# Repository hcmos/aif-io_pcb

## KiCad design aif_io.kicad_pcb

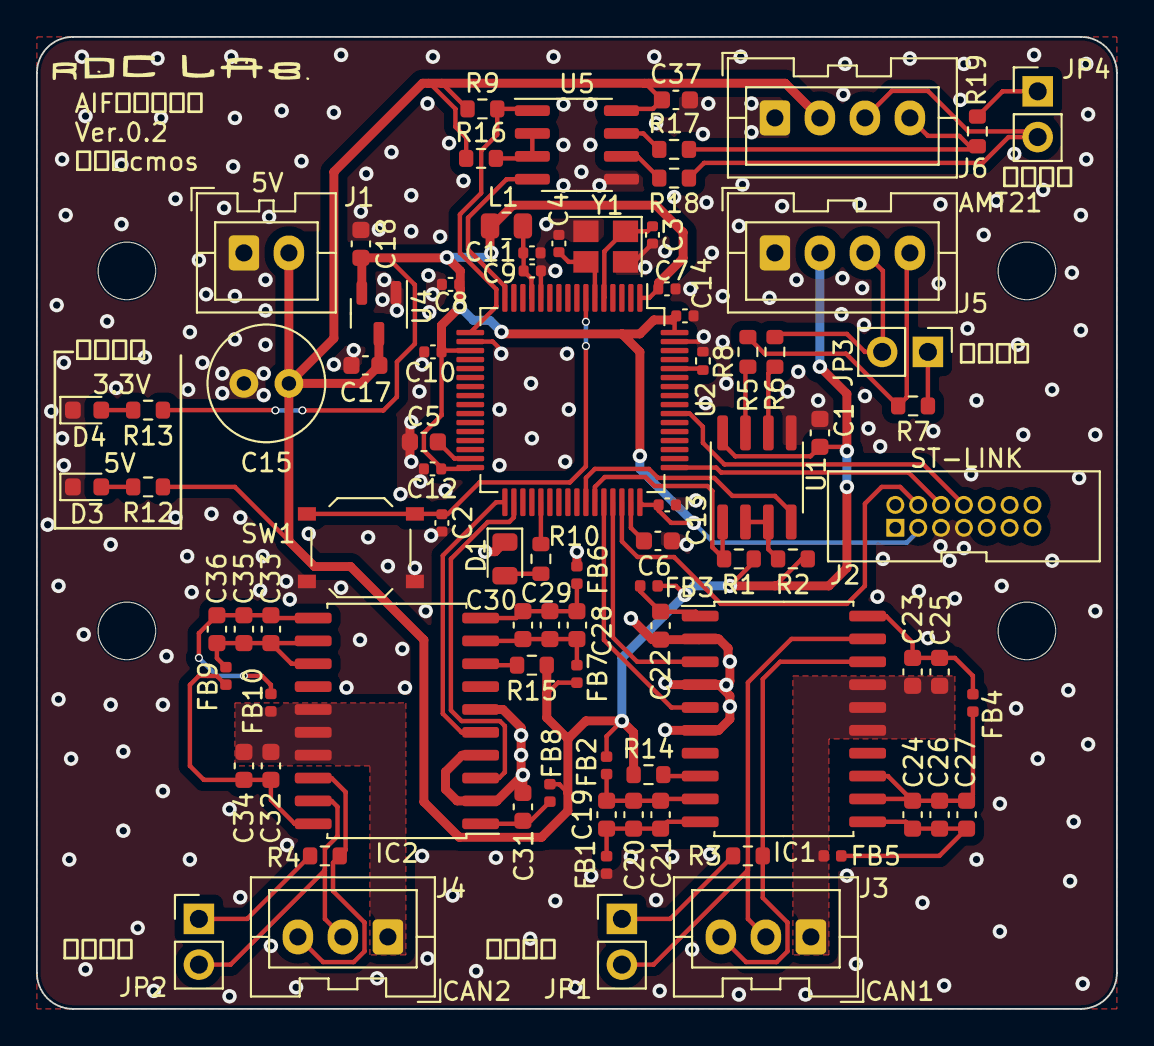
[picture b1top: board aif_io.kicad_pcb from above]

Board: 2 copper layers, 60.0 x 54.0 mm, 90 parts (0 on the bottom side), 59 nets.

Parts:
C1, C22, C23, C31, C32, C37: 0.1u; C_0603_1608Metric
C2, C7, C10, C11, C12, C13, C14: 0.1u; C_0402_1005Metric
C3, C4: 18p; C_0402_1005Metric
C5, C6: 2.2u; C_0603_1608Metric
C8: 4.7u; C_0402_1005Metric
C9: 1u; C_0402_1005Metric
C15: 100u; C_Radial_D6.3mm_H11.0mm_P2.50mm
C17, C18, C20, C26, C29, C35: 1u; C_0603_1608Metric
C19, C25, C27, C28, C34, C36: 10u; C_0603_1608Metric
C21, C24, C30, C33: 10n; C_0603_1608Metric
D1: LED; LED_0805_2012Metric
D3, D4: LED; LED_0603_1608Metric
FB1, FB2, FB3, FB4, FB5, FB6, FB7, FB8, FB9, FB10: FerriteBead; L_0402_1005Metric
H1, H2, H3, H4: MountingHole; MountingHole_3.2mm_M3
IC1, IC2: ISOW1044BDFMR; SOIC-20W_7.5x12.8mm_P1.27mm
J1: PWR; JST_XA_B02B-XASK-1_1x02_P2.50mm_Vertical
J2: ST-LINK; JTAG_BOX_CONN
J3, J4: CAN; JST_XA_B03B-XASK-1_1x03_P2.50mm_Vertical
J5, J6: AMT21; JST_XA_B04B-XASK-1_1x04_P2.50mm_Vertical
JP1, JP2, JP3, JP4: Jumper_2_Open; PinHeader_1x02_P2.54mm_Vertical
L1: 600@100MHz; R_0805_2012Metric
R1, R2, R9, R16: 10k; R_0603_1608Metric
R3, R4, R7, R19: 120; R_0603_1608Metric
R5, R6, R17, R18: 10; R_0603_1608Metric
R8: 10k; R_0402_1005Metric
R10, R13: 1.2k; R_0603_1608Metric
R12: 3.3k; R_0603_1608Metric
R14, R15: 4.7k; R_0603_1608Metric
SW1: SW_Push; SW_Push_1P1T_XKB_TS-1187A
U1, U5: THVD1420D; SOIC-8_3.9x4.9mm_P1.27mm
U2: STM32F405RGTx; LQFP-64_10x10mm_P0.5mm
U4: XC6206P332MR; SOT-23-3
Y1: 25MHz; Crystal_SMD_3225-4Pin_3.2x2.5mm

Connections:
+3.3V: C7.1, C8.1, C10.1, C12.1, C13.1, C14.1, C18.1, J2.3, L1.1, R13.1, U2.1 (VBAT), U2.19 (VDD), U2.32 (VDD), U2.48 (VDD), U2.64 (VDD), U4.2 (VO)
+5V: C1.1, C15.1, C17.1, C37.1, FB2.1, FB3.1, FB7.1, FB8.1, J1.2, J5.2, J6.2, R1.1, R2.1, R9.1, R12.1, R14.1, R15.1, R16.1, U1.8 (VCC), U4.3 (VI), U5.8 (VCC)
/CAN_Transceiver1/CAN_H: IC1.19 (CANH), J3.2, JP1.2 (B)
/CAN_Transceiver1/CAN_L: IC1.18 (CANL), J3.3, R3.2
/CAN_Transceiver1/CAN_RX: IC1.5 (RXD), U2.44 (PA11)
/CAN_Transceiver1/CAN_TX: IC1.3 (TXD), U2.45 (PA12)
/CAN_Transceiver1/GND_CAN: C23.2, C25.2, FB5.2, IC1.15 (GISOIN_1), IC1.16 (GISOIN_2), IC1.17 (GISOIN_3), J3.1
/CAN_Transceiver2/CAN_H: IC2.19 (CANH), J4.2, JP2.2 (B)
/CAN_Transceiver2/CAN_L: IC2.18 (CANL), J4.3, R4.2
/CAN_Transceiver2/CAN_RX: IC2.5 (RXD), U2.33 (PB12)
/CAN_Transceiver2/CAN_TX: IC2.3 (TXD), U2.34 (PB13)
/CAN_Transceiver2/GND_CAN: C32.2, C34.2, FB10.2, IC2.15 (GISOIN_1), IC2.16 (GISOIN_2), IC2.17 (GISOIN_3), J4.1
/CYCLE_LED: R10.1, U2.37 (PC6)
/STM32F405/SWCLK: J2.6, U2.49 (PA14)
/STM32F405/SWDIO: J2.4, U2.46 (PA13)
/STM32F405/SWO: J2.8, U2.55 (PB3)
/USART1_RX: R1.2, U1.1 (RO), U2.43 (PA10)
/USART1_TX: U1.4 (DI), U2.42 (PA9)
/USART2_RX: R9.2, U2.17 (PA3), U5.1 (RO)
/USART2_TX: U2.16 (PA2), U5.4 (DI)
GND: C1.2, C2.2, C3.2, C4.2, C5.2, C6.2, C7.2, C8.2, C9.2, C10.2, C11.2, C12.2, C13.2, C14.2, C15.2, C17.2, C18.2, C22.2, C31.2, C37.2, D1.1 (K), D3.1 (K), D4.1 (K), FB1.1, FB6.1, IC1.2 (IN), IC1.4 (STB), IC1.6 (GNDIO), IC2.2 (IN), IC2.4 (STB), IC2.6 (GNDIO), J1.1, J2.5, J2.7, J5.1, J6.1, R8.2, SW1.1, U1.5 (GND), U2.12 (VSSA), U2.18 (VSS), U2.63 (VSS), U4.1 (GND), U5.5 (GND), Y1.2, Y1.4
unnamed: D1.2 (A), R10.2
unnamed: D3.2 (A), R12.2
unnamed: D4.2 (A), R13.2
unnamed: IC1.8 (EN/FLT), R14.2
unnamed: C19.2, C20.2, C21.2, FB1.2, IC1.10 (GND1)
unnamed: C24.2, C26.2, C27.2, FB5.1, IC1.11 (GND2)
unnamed: C19.1, C20.1, C21.1, FB2.2, IC1.9 (VDD)
unnamed: C22.1, FB3.2, IC1.1 (VIO)
unnamed: C23.1, C25.1, FB4.2, IC1.20 (VISOIN)
unnamed: C24.1, C26.1, C27.1, FB4.1, IC1.12 (VISOOUT), IC1.13 (VSIN)
unnamed: IC2.8 (EN/FLT), R15.2
unnamed: C28.2, C29.2, C30.2, FB6.2, IC2.10 (GND1)
unnamed: C33.2, C35.2, C36.2, FB10.1, IC2.11 (GND2)
unnamed: C28.1, C29.1, C30.1, FB7.2, IC2.9 (VDD)
unnamed: C31.1, FB8.2, IC2.1 (VIO)
unnamed: C32.1, C34.1, FB9.2, IC2.20 (VISOIN)
unnamed: C33.1, C35.1, C36.1, FB9.1, IC2.12 (VISOOUT), IC2.13 (VSIN)
unnamed: J5.3, JP3.2 (B), R6.2
unnamed: J5.4, R5.2, R7.2
unnamed: J6.3, JP4.2 (B), R18.2
unnamed: J6.4, R17.2, R19.2
unnamed: JP1.1 (A), R3.1
unnamed: JP2.1 (A), R4.1
unnamed: JP3.1 (A), R7.1
unnamed: JP4.1 (A), R19.1
unnamed: R6.1, U1.6 (A)
unnamed: R5.1, U1.7 (B)
unnamed: R2.2, U1.2 (~RE), U1.3 (DE)
unnamed: R8.1, U2.60 (BOOT0)
unnamed: C2.1, SW1.2, U2.7 (NRST)
unnamed: C3.1, U2.5 (PH0), Y1.1
unnamed: C4.1, U2.6 (PH1), Y1.3
unnamed: C5.1, U2.31 (VCAP_1)
unnamed: C6.1, U2.47 (VCAP_2)
unnamed: R18.1, U5.6 (A)
unnamed: R17.1, U5.7 (B)
unnamed: R16.2, U5.2 (~RE), U5.3 (DE)
VDDA: C9.1, C11.1, L1.2, U2.13 (VDDA)

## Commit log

2025-09-06 first sch
2025-12-15 v0.2
2025-12-15 sch pdf
